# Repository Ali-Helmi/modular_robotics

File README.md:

# Modular Robotics (Molucubes)
A repository which holds all the files for the subsystems that make up our senior design project.

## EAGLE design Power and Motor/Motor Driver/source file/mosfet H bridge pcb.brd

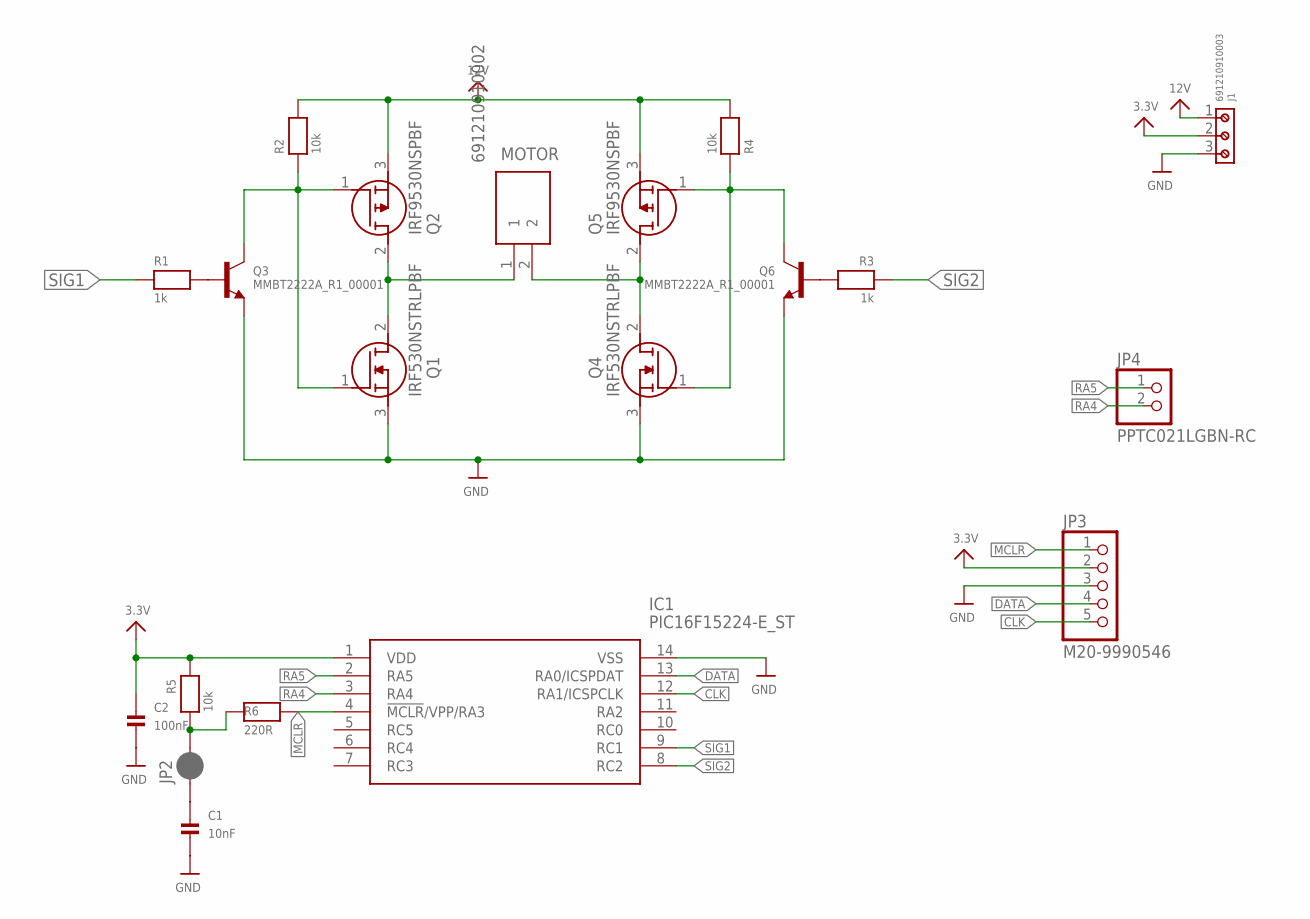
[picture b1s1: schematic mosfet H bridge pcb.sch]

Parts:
C1: 10nF; _0603
C2: 100nF; _0603
IC1: PIC16F15224-E_ST; SOP65P640X120-14N
J1: 691210910003
JP2: JUMPER-SMT_2_NC_PASTE_SILK; SMT-JUMPER_2_NC_PASTE_SILK
JP3: M20-9990546; 1X05_ROUND
JP4: PPTC021LGBN-RC; 1X02/90
MOTOR: 691210910002
Q1, Q4: IRF530NSTRLPBF; IRF2804STRLPBF
Q2, Q5: IRF9530NSPBF; IDB30E60
Q3, Q6: MMBT2222A_R1_00001; SOT23-R
R1, R3: 1k; _0603
R2, R4, R5: 10k; _0603
R6: 220R; _0603

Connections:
3.3V: C2.1, IC1.1 (VDD), J1.2, JP3.2, R5.2
12V: J1.1, Q2.3 (S), Q5.3 (S), R2.2, R4.2
CLK: IC1.12 (RA1/ICSPCLK), JP3.5
DATA: IC1.13 (RA0/ICSPDAT), JP3.4
GND: C1.2, C2.2, IC1.14 (VSS), J1.3, JP3.3, Q1.3 (S), Q3.2 (E), Q4.3 (S), Q6.2 (E)
MCLR: IC1.4 (!MCLR!/VPP/RA3), JP3.1, R6.2
unnamed: Q3.1 (B), R1.2
unnamed: Q1.1 (G), Q2.1 (G), Q3.3 (C), R2.1
unnamed: C1.1, JP2.1
unnamed: MOTOR.1, Q1.2 (D), Q2.2 (D)
unnamed: Q6.1 (B), R3.2
unnamed: Q4.1 (G), Q5.1 (G), Q6.3 (C), R4.1
unnamed: MOTOR.2, Q4.2 (D), Q5.2 (D)
unnamed: JP2.2, R5.1, R6.1
RA4: IC1.3 (RA4), JP4.2
RA5: IC1.2 (RA5), JP4.1
SIG1: IC1.9 (RC1), R1.1
SIG2: IC1.8 (RC2), R3.1

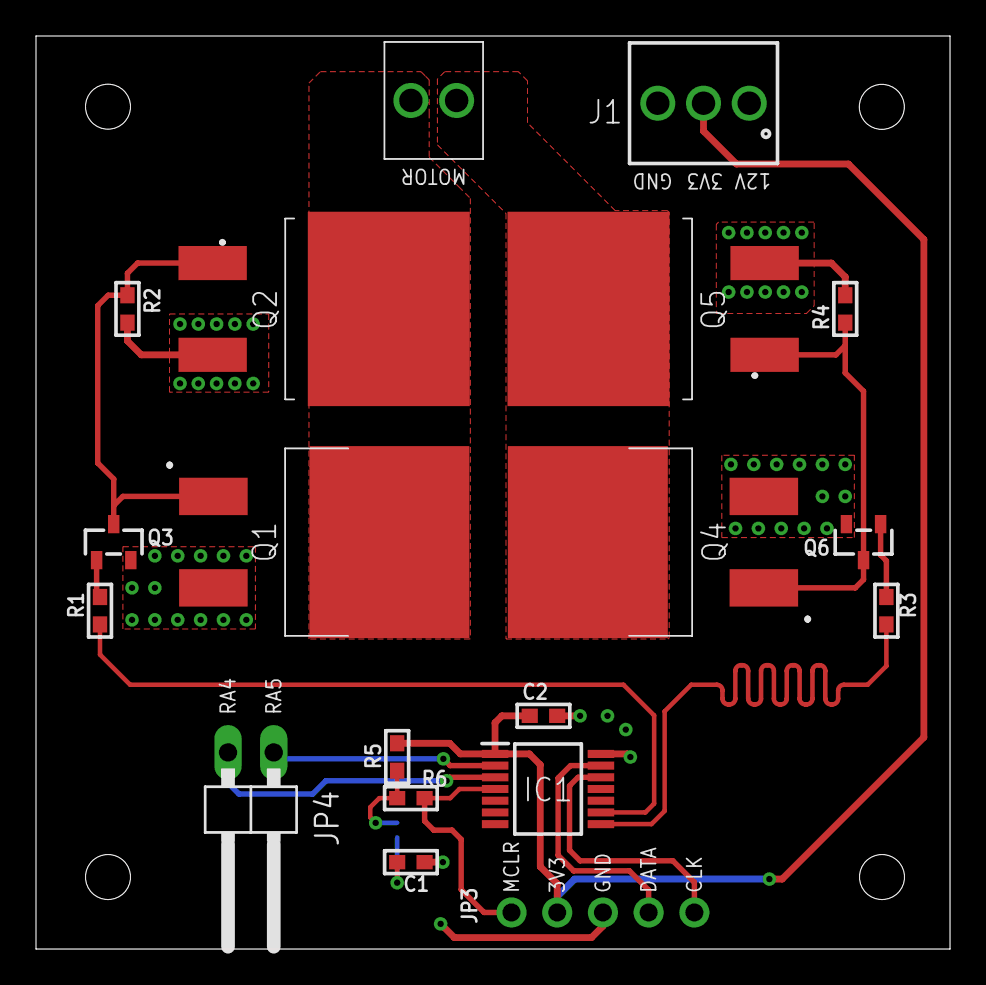
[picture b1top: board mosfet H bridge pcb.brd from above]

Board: 2 copper layers, 50.8 x 50.7 mm, 20 parts (1 on the bottom side), 18 nets.

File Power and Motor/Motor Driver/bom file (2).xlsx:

Qty | Value | Device | Package | Parts | Description
1 | 100nF | CAP_CERAMIC_0603 | _0603 | C2 | Ceramic Capacitors
3 | 10k | RESISTOR_0603 | _0603 | R2, R4, R5 | Resistors
1 | 10nF | CAP_CERAMIC_0603 | _0603 | C1 | Ceramic Capacitors
2 | 1k | RESISTOR_0603 | _0603 | R1, R3 | Resistors
1 | 220R | RESISTOR_0603 | _0603 | R6 | Resistors
1 | 691210910002 | 691210910002 | 691210910002 | MOTOR | Wurth Elektronik, 2109 2.54mm Pitch, 2 Way PCB Terminal Block
1 | 691210910003 | 691210910003 | 691210910003 | J1 | WR-TBL Serie 2109 - 2.54 mm Horiz. Entry
2 | IRF530NSTRLPBF | IRF530NSTRLPBF | IRF2804STRLPBF | Q1, Q4 | IRF530NSTRLPBF N-Channel MOSFET, 17 A, 100 V HEXFET, 3-Pin D2PAK Infineon
2 | IRF9530NSPBF | IRF9530NSPBF | IDB30E60 | Q2, Q5 | IRF9530NSPBF P-Channel MOSFET, 14 A, 100 V HEXFET, 3-Pin D2PAK Infineon
1 | JUMPER-SMT_2_NC_PASTE_SILK | JUMPER-SMT_2_NC_PASTE_SILK | SMT-JUMPER_2_NC_PASTE_SILK | JP2 | Normally closed solder jumper
1 | M20-9990546 | HEADER-1X5ROUND | 1X05_ROUND | JP3 | PIN HEADER
2 | MMBT2222A_R1_00001 | TRANSISTOR_NPN | SOT23-R | Q3, Q6 | NPN Transistor
1 | PIC16F15224-E_ST | PIC16F15224-E_ST | SOP65P640X120-14N | IC1 | 8-bit Microcontrollers - MCU 7KB Flash, 512B RAM, 10b ADC, 2x PWM, 2x CCP, HLT,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
1 | PPTC021LGBN-RC | PINHD-1X2/90 | 1X02/90 | JP4 | PIN HEADER

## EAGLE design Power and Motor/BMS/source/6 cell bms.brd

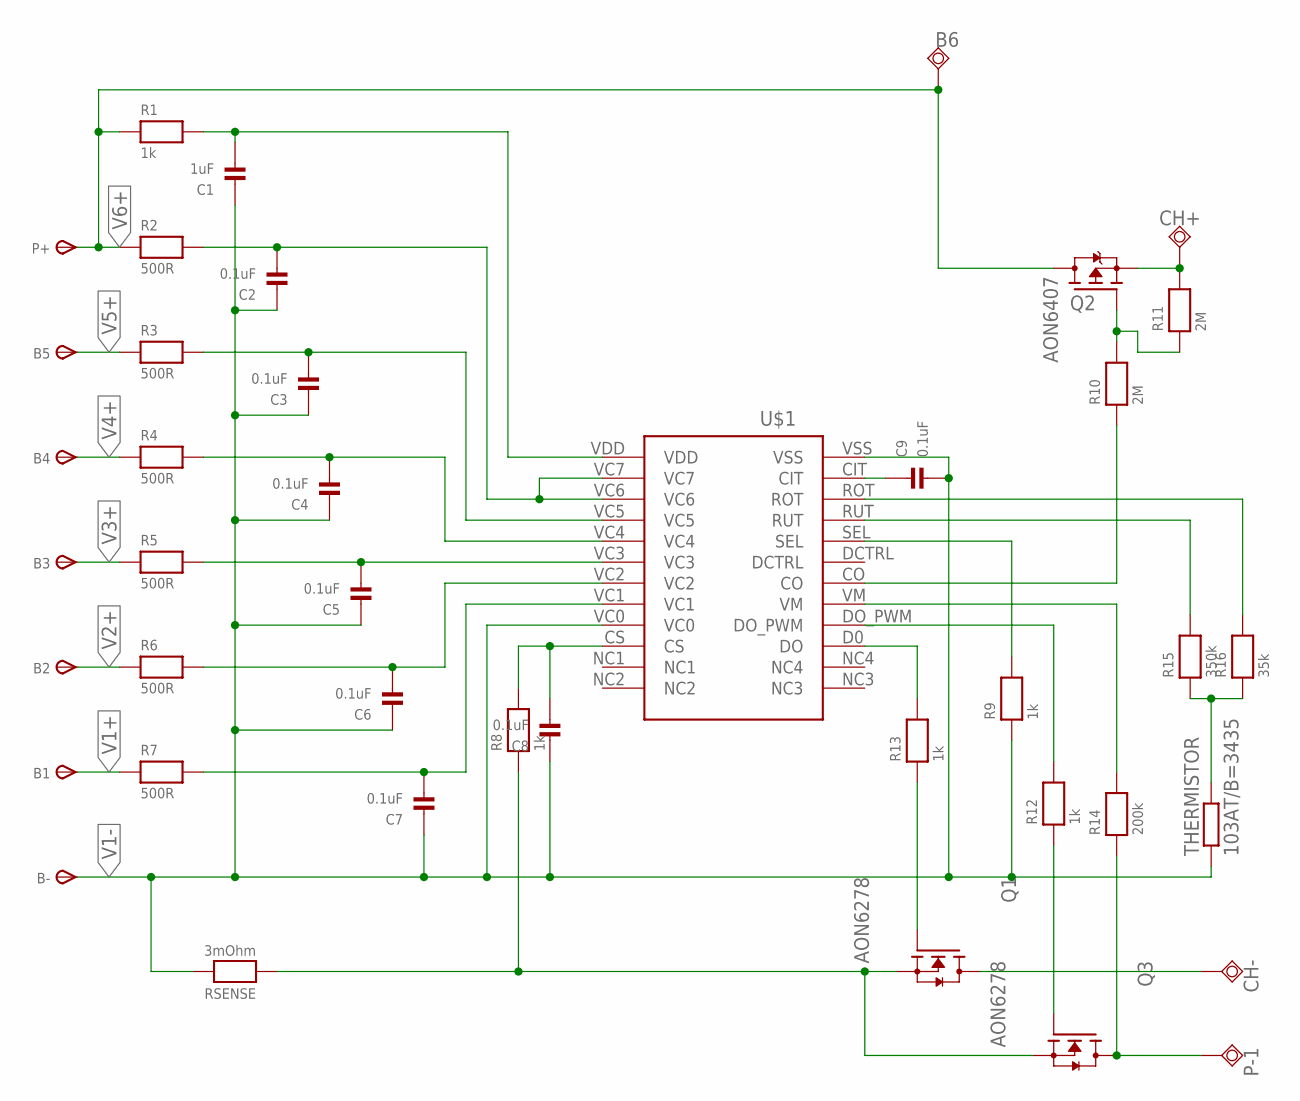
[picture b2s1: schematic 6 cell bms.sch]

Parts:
B1, B2, B3, B4, B5: TPSTP20SQ; TP20SQ
B6: TPSQTP20SQ; TP20SQ
B-: TPSTP20SQ; TP20SQ
C1: 1uF; _0603
C2, C3, C4, C5, C6, C7, C8, C9: 0.1uF; _0603
CH+: TPSQTP20SQ; TP20SQ
CH-: TPSQTP20SQ; TP20SQ
P+: TPSTP20SQ; TP20SQ
P-1: TPSQTP20SQ; TP20SQ
Q1, Q3: AON6278; TRANS_AON6278
Q2: AON6407; TRANS_AON6407
R1: 1k; _0805
R2, R3, R4, R5, R6, R7: 500R; _0805
R8, R9, R12, R13: 1k; _0603
R10, R11: 2M; _0603
R14: 200k; _0603
R15: 350k; _0603
R16: 35k; _0603
RSENSE: 3mOhm; 2512
THERMISTOR: 103AT/B=3435; 0204V
U$1: CW1073

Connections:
unnamed: C1.2, R1.2, U$1.VDD
unnamed: C2.2, R2.2, U$1.VC6, U$1.VC7
unnamed: C3.2, R3.2, U$1.VC5
unnamed: Q2.4 (G), R10.2, R11.1
unnamed: R9.2, U$1.SEL
unnamed: R10.1, U$1.CO
unnamed: CH+.TP, Q2.1 (S), Q2.2 (S), Q2.3 (S), R11.2
unnamed: C4.2, R4.2, U$1.VC4
unnamed: Q3.4 (G), R12.1
unnamed: Q1.4 (G), R13.1
unnamed: R13.2, U$1.D0 (DO)
unnamed: C8.2, R8.2, U$1.CS
unnamed: Q1.1 (S), Q1.2 (S), Q1.3 (S), Q3.1 (S), Q3.2 (S), Q3.3 (S), R8.1, RSENSE.1
unnamed: C9.1, U$1.CIT
unnamed: R12.2, U$1.DO_PWM
unnamed: R14.2, U$1.VM
unnamed: P-1.TP, Q3.5 (D), Q3.6 (D), Q3.7 (D), Q3.8 (D), Q3.9 (D), R14.1
unnamed: CH-.TP, Q1.5 (D), Q1.6 (D), Q1.7 (D), Q1.8 (D), Q1.9 (D)
unnamed: R16.2, U$1.ROT
unnamed: C5.2, R5.2, U$1.VC3
unnamed: R15.2, U$1.RUT
unnamed: R15.1, R16.1, THERMISTOR.2
unnamed: C6.2, R6.2, U$1.VC2
unnamed: C7.2, R7.2, U$1.VC1
V1+: B1.TP, R7.1
V1-: B-.TP, C1.1, C2.1, C3.1, C4.1, C5.1, C6.1, C7.1, C8.1, C9.2, R9.1, RSENSE.2, THERMISTOR.1, U$1.VC0, U$1.VSS
V2+: B2.TP, R6.1
V3+: B3.TP, R5.1
V4+: B4.TP, R4.1
V5+: B5.TP, R3.1
V6+: B6.TP, P+.TP, Q2.5_8 (D), R1.1, R2.1

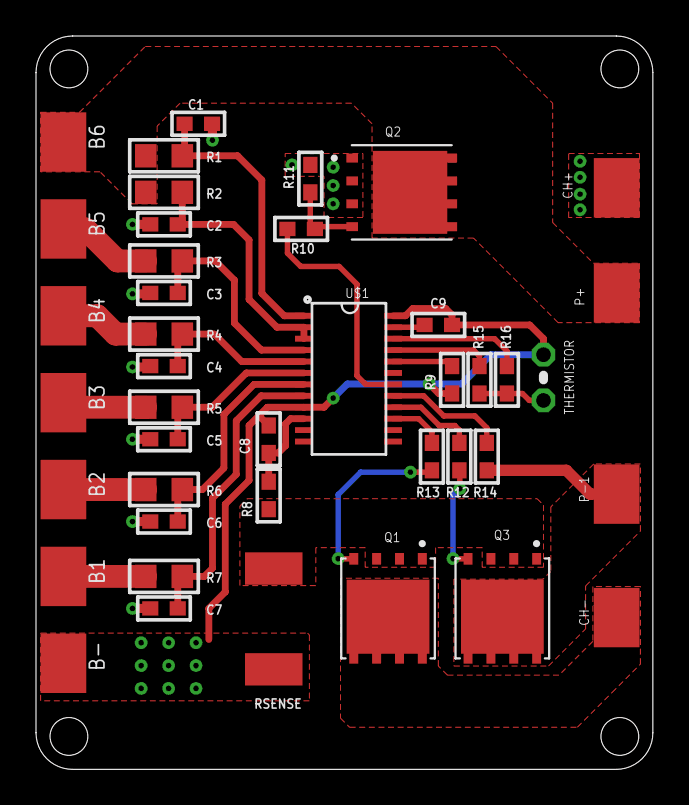
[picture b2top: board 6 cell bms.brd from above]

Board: 2 copper layers, 34.3 x 40.7 mm, 42 parts (0 on the bottom side), 31 nets.

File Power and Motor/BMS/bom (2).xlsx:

Qty | Value | Device | Package | Parts | Description
8 | 0.1uF | CAP_CERAMIC_0603 | _0603 | C2, C3, C4, C5, C6, C7, C8, C9 | Ceramic Capacitors
1 | 103AT/B=3435 | R-EU_0204/2V | 0204V | THERMISTOR | RESISTOR, European symbol | https://www.mouser.com/ProductDetail/Vishay-BC-Components/NT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
4 | 1k | RESISTOR_0603 | _0603 | R8, R9, R12, R13 | Resistors
1 | 1k | RESISTOR_0805 | _0805 | R1 | Resistors
1 | 1uF | CAP_CERAMIC_0603 | _0603 | C1 | Ceramic Capacitors
1 | 200k | RESISTOR_0603 | _0603 | R14 | Resistors
2 | 2M | RESISTOR_0603 | _0603 | R10, R11 | Resistors
1 | 350k | RESISTOR_0603 | _0603 | R15 | Resistors
1 | 35k | RESISTOR_0603 | _0603 | R16 | Resistors
1 | 3mOhm | RESISTOR2512 | 2512 | RSENSE | Resistors | https://www.digikey.com/en/products/detail/bourns-inc/CRE251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
6 | 500R | RESISTOR_0805 | _0805 | R2, R3, R4, R5, R6, R7 | Resistors
2 | AON6278 | AON6278 | TRANS_AON6278 | Q1, Q3 | Trans MOSFET N-CH 80V 85A 8-Pin DFN EP Check availability | https://www.digikey.com/en/products/detail/alpha-omega-semic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
1 | AON6407 | AON6407 | TRANS_AON6407 | Q2 | P-Channel 30V 32A (Ta), 85A (Tc) 7.3W (Ta), 83W (Tc) Surface Mount 8-DFN (5x6) 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 | https://www.digikey.com/en/products/detail/alpha-omega-semic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
1 | CW1073 | CW1073 | CW1073 | U$1

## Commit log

2022-12-04 Created subsystem folders
2022-12-05 Raspberry Pi and MCU files
2022-12-05 Create Buck Converters
2022-12-05 Update Buck Converters
2022-12-05 Power and motor files
2022-12-05 Datasheets for power and motor
2022-12-05 Gripper Arm & Object Detection Files
    Initial commit
2022-12-05 Report Documents
2023-01-30 Moving RPi and MCU code to its own folder. Created a basic framework for the main python program as well as the beginnings of the robot script. Updated the motor control code to fit with the latest m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
2023-01-30 Created weekly updates folder
2023-02-09 Weekly update
2023-02-10 Create Ali Helmi.txt
    The weekly update text file
2023-02-12 Created test scripts for testing on PC. Updated controller, robot, and comms scripts
2023-02-13 Object Detection Integration
    Adding queue as an argument to the function, and appending to it desired objects every frame.
2023-02-13 Fixed UART comms to no longer lock up MCUs, updated robot script to communicate a bit faster
2023-02-18 Integrated object detection code into controller script, and added a basic searching script to look for and move towards ping pong balls. Updated obejct detection script with needed data format.
2023-04-12 Object Detection & Gripper Arm Updates
    Weekly updates, and updated supporting files for both object detection and gripper arm.
2023-04-12 Weekly Updates and Code Updates
    Weekly updates and updated code for the MCUs and RPi
2023-04-12 Object Detection & Gripper Arm Updates
    Training demos including confusion matrix and other graphs.
2023-04-12 Updated yolov8_detection.py
    added size
2023-04-24 Updates for Ali Helmi
    Weekly Update of April 19th
2023-04-24 edits
    weekly update
2023-04-27 Power and Motor Updates

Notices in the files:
parts and their libraries:
microbuilder: This work is placed in the public domain, and may be freely used for commercial and non-commercial work with the following conditions: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
SparkFun-Jumpers: Licensing: Creative Commons ShareAlike 4.0 International - https://creativecommons.org/licenses/by-sa/4.0
